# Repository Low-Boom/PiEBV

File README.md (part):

# PiEBV

A USB-controlled pulse-timing box for particle image velocimetry (PIV), built around a Raspberry
Pi Pico 2 W. It triggers two laser drivers and synchronizes up to six event cameras.

> **Hardware status:** Firmware timing has not yet been verified on a physical board. Complete the
> [first-board checks](Hardware.md#first-board-checks) before connecting a laser driver or camera.

## Quick start

With the assembled board, a Pico 2 W, a USB-C PD charger that supplies 15 V, and a micro-USB data
cable:

```
python -m pip install platformio
pio run
```

1. Follow the [first-board checks](Hardware.md#first-board-checks) before applying power or
   connecting equipment.
2. Flash `.pio/build/pico2w/firmware.uf2`: hold **BOOTSEL** while connecting the Pico's micro-USB
   cable, then copy the UF2 to the `RP2350` drive. Flash with the Pico out of the board or J17
   unplugged.
3. Seat the Pico components-up, USB toward the board's left edge. Set J10 to **2-3** and J18, J19
   and J21 to **1-2** for the 50 Ω scope checks; leave J11 empty until instructed to check the outputs.
4. Connect the 15 V charger to J17 and the Pico's micro-USB to the computer. Open the Pico's serial
   port, enable local echo, and send `STATUS`.
5. Follow [Hardware setup](#hardware-setup) to check the laser outputs with a scope before
   connecting laser drivers or cameras.

**Contents:** [Quick start](#quick-start) · [What it does](#what-it-does) ·
[Safety](#safety) · [The board](#the-board) · [Hardware setup](#hardware-setup) ·
[Connecting](#connecting) · [Command reference](#command-reference) ·
[Troubleshooting](#troubleshooting) · [Building from source](#building-from-source) ·
[Repository layout](#repository-layout)

---

## What it does

| Output | Connector | What it is for |
|---|---|---|
| **Laser 1** (CH1) | BNC J7 | Trigger for the first laser driver: a 5 V pulse (with J18 set to match the input), `WIDTH` long, `FREQ` times per second |
| **Laser 2** (CH2) | BNC J8 | Trigger for the second laser driver: the same pulse, starting exactly `DELAY` after Laser 1 |
| **Sync** | Camera ports J1–J6 | A steady 1 MHz clock that all six cameras keep time by |
| **Trigger** (the marker) | Camera ports J1–J6 | A pulse at the same instant as every Laser 1 pulse. Each camera records it as a timestamp in its data. (Jumper J10 can switch the cameras to the Laser 1 pulse itself instead.) |
| **Pixel reset** | Camera ports J1–J6 | Holds the camera sensors blank between flash pairs. Controlled only by PiEBV (`PIXGATE`) |
| **External Sync Out** | BNC J12 | A copy of the camera trigger (the marker, or Laser 1 with J10 on 1-2) for other equipment: a 5 V pulse, with J21 set to match the input |

- Every signal to the cameras is **1.8 V** (IDS cameras, J22 open) or **3.3 V** (Prophesee EVK4
  cameras, J22 fitted). The laser outputs and External Sync Out are **5 V**.
- The camera signal level comes from a power mux (U20). Its default input is 1.8 V: with J22 open,
  two pull-up resistors in parallel (R34 and R70) select 1.8 V. A shunt on J22 pulls the select pin low and selects
  3.3 V.
- Each camera line has a **47 Ω series resistor on the board** (R52–R69), between the buffer and
  the camera port. It terminates the camera cable at the source. The camera cables need no
  resistors.
- The camera lines of each group have **equal length** on the board, from the buffer to the series
  resistor: Sync 74.082 mm, Trigger 43.584 mm, pixel reset 51.472 mm (spread below 0.001 mm in
  each group, KiCad's length reading).
- Times are set in steps of **6.667 ns** (one tick of the Pico's 150 MHz clock), or **3.333 ns**
  with a shunt on the clock jumper J20 (a 300 MHz overclock; see [Jumpers](#jumpers)).
  Every reply shows the exact value the hardware will produce, so you never have to correct for the
  step size.
- Both laser pulses share one `WIDTH` and one `FREQ`.
- The firmware sets **no laser-driver limits** (pulse width, duty, spacing). Set what your driver is
  rated for. It only stops the pulses from running into each other.

PiEBV was designed for two **PicoLas LDP-V** laser-diode drivers (models 10-70 and 240-100) and six
**IDS uEye UE-39B0XCP-E** event cameras. Board revision 2 can also drive six **Prophesee EVK4**
cameras at 3.3 V (see the [EVK4 harness](docs/EVK4_HARNESS.md)). Other drivers with a 5 V trigger input should work too, with
the output mode (J18/J19) set to match their input.

---

## Safety

### The short version

1. **The lasers start off.** At every power-up and every reset the laser outputs are DISARMED. They
   pulse only after you send `ARM`.
2. **Typing `DISARM` stops them at once.**
3. **Three things must all be true** for the lasers to pulse. Remove any one and they stop:
   - the firmware is ARMED;
   - a shunt is on **J11 pins 1-2** (or a closed E-stop switch is wired there);
   - a 15 V USB-C charger is plugged into **J17**.
4. **Unplugging the computer does not stop the lasers.** Use J11 or J17 for that.
5. **Set each output's mode (J18, J19, J21) before you connect anything to it.**
6. **One laser driver per output.** Never split an output with a BNC tee, and never join J7 and J8.
7. **Cameras:** build the harness with wires 2, 3, 4, 5 and 7 only, and set every camera to sync
   slave.

### In detail

**Starting and stopping**

- **`DISARM` always works, immediately.** The six letters D-I-S-A-R-M, in any case and anywhere in
  what you type, disarm the outputs as soon as the last letter reaches the board. You don't need to
  press Enter, as long as your terminal sends each key as you type it (all the terminals listed
  under [USB serial](#usb-serial) do). A monitor with a separate input box, such as the Arduino
  IDE's, sends nothing until you press Enter.
- **The three gates are independent.** Each one on its own holds both outputs at 0 V. The firmware
  can only see the first one, so `ARMED=1` does not by itself mean the outputs are live. The third
  gate (U18) checks that the board's 12 V laser-driver supply is between 10.6 and 13.3 V, which needs
  the 15 V charger.
- **Losing the USB link does not disarm.** If the Pico's USB cable is pulled, the PC goes to sleep
  or a script is killed while ARMED, the board keeps running from J17 and the lasers keep pulsing,
  with no way to send `DISARM`. Stop them in hardware: take the J11 shunt off 1-2, or unplug J17.
- **Before uploading new firmware, send `DISARM`.** The upload restarts the Pico, and a restart in
  the middle of a pulse can stretch that one pulse by an estimated 70–150 ns.
- **Before using a debugger (SWD), send `DISARM` and remove the J11 shunt** (or unplug J17). A
  debugger reset can leave a laser output high for milliseconds.

**Laser outputs**

- **Match the output mode to what you connect.** J18 sets the mode for J7 (Laser 1), J19 for J8
  (Laser 2) and J21 for J12 (External Sync Out) ([details](#jumpers)):

  | Shunt | Mode | Use it for | Into a 50 Ω input | Into a Hi-Z input |
  |---|---|---|---|---|
  | **1-2** | 50 Ω | The LDP-V, or any 50 Ω input | **about 4.8 V** (correct) | about 12 V (too high for 5 V logic) |
  | **2-3** | Hi-Z | TTL or 5 V CMOS inputs, a scope at 1 MΩ | about 2.5 V (too low to fire an LDP-V) | **about 4.8 V** (correct) |
  | none | — | nothing: always fit a shunt | about 3.5 V | about 12 V |

  To fire **one light source with both pulses**, or **two light sources together with the same
  double pulse**, use `COMBINE 1` instead ([Combined mode](#combined-mode-combine)): each output
  then carries both pulses, still one driver per output.

**Cameras and jumpers**

- **Camera pins 1, 6 and 8 are not connected on the board,** so a straight-through ribbon can't
  short the camera's own supplies at the board (pin 1 is the camera's 1.8 V output, pin 8 its USB
  5 V). The remaining risk is in the harness: fit only wires 2, 3, 4, 5 and 7 (or cut 1, 6 and 8),
  and never join pin 1 or 8 to a ground wire. Pin 6 is undocumented: don't assume it is a ground.
- **Set every camera to sync slave.** PiEBV drives the sync pin, so a camera set as sync master would
  fight it.
- **Never fit a shunt across all three pins of J10.**
- **Don't short J12.** External Sync Out can be high for up to half the period (`MARKERWIDTH` is
  limited to 50 % for this reason); into a short its 2 W, 68 Ω resistor then takes up to 1.1 W on
  average (1.45 W with J10 on 1-2 and `COMBINE 1`).

More detail: [Hardware.md](Hardware.md), sections Boot and arming, Laser
interlock and Connectors.

---

## The board

The board is a **EuroCard, 160 × 100 mm**. Orientation used below: the board is landscape (160 mm
wide), seen from the top side. All connectors are on the two short edges: the Pico's micro-USB,
TP3 and, at the bottom, the USB-C connector J17 on the **left** edge, and only the three BNCs on
the **right** edge. The Pico plugs into two horizontal sockets at the top left, with its micro-USB at
the left edge, and the six camera ports run in one row along the bottom. The two USB ports are
labelled on the board: **`CONTROL / PROGRAM — PICO MICRO-USB`** (commands and firmware) and
**`POWER ONLY — USB-C PD 15 V`** (J17). The long (160 mm) edges have no parts within 2.5 mm, so the
board fits EuroCard card guides and slotted enclosures.

```
             +------------------------------------------------------------+
 Pico USB    |= Pico 2 W, in J15 (top row)                        J18 J7 =|  Laser 1 (BNC)
 = CONTROL   |  and J14 (bottom row)        J10 (trigger select)          |
             |= TP3 (1 MHz scope)  J20 (clock)                    J19 J8 =|  Laser 2 (BNC)
             |  J12 offset field            J11 (laser enable)            |
             |                                                   J21 J12 =|  External Sync Out (BNC)
 USB-C       |= J17                                                       |
 = POWER ONLY|       J1   J2   J3   J4   J5   J6   (camera ports)         |
             +------------------------------------------------------------+
```

(Not to scale. J18, J19 and J21 are the output-mode jumpers. J22, at the top centre, sets the camera signal level.
The status LEDs are near the top edge. Images of the board are in
[Hardware.md](Hardware.md#board-views).)

### Connectors

| Ref | What | Connect to | Notes |
|---|---|---|---|
| **J1–J6** | Camera ports 1–6 (2×5 IDC headers) | Each camera's 8-pin I/O cable (header pin *n* = camera pin *n*) | Pin 2, 7 ground · 3 pixel reset · 4 trigger · 5 sync · 1, 6, 8, 9, 10 not connected. All signals **1.8 V** (J22 open, IDS cameras) or **3.3 V** (J22 fitted, Prophesee EVK4 with the [EVK4 harness](docs/EVK4_HARNESS.md)). Each signal has a 47 Ω series resistor on the board. Pin 1 is the top-left pin. |
| **J7** | BNC, Laser 1 (CH1) | First laser driver's trigger input | Mode set by J18 |
| **J8** | BNC, Laser 2 (CH2) | Second laser driver's trigger input | Mode set by J19 |
| **J12** | BNC, External Sync Out | Equipment that must follow the camera trigger (50 Ω or Hi-Z input) | Mode set by J21. See [J12](#j12--external-sync-out) below |
| **J17** | USB-C, **power only** | A USB-C PD charger that offers 15 V | No data. Commands and firmware go through the Pico's own micro-USB. |
| **J10** | Camera trigger source (jumper) | A shunt | See [Jumpers](#jumpers) |
| **J11** | Laser enable (jumper) | A shunt, or a normally-closed E-stop switch | See [Jumpers](#jumpers) |
| **J18**, **J19**, **J21** | Output mode (jumpers; J18 = Laser 1, J19 = Laser 2, J21 = External Sync Out) | A shunt | See [Jumpers](#jumpers) |
| **J20** | Clock jumper, 2-pin header right of the Pico, below the J14 row | Nothing (150 MHz), or a shunt (300 MHz overclock) | See [Jumpers](#jumpers). Leave it open unless that Pico passed the soak test. |
| **TP3** | 2-pin header on the left edge, below the Pico | A scope | Pin 1 = the 1 MHz sync straight from the Pico (3.3 V) · pin 2 = ground |
| **J22** | Camera signal level, 2-pin header at the top centre | Nothing (1.8 V, IDS cameras), or a shunt (3.3 V, Prophesee EVK4) | See [Jumpers](#jumpers). **Never fit it with an IDS camera connected.** |
| **TP4–TP9** | Bare test pads at the top centre, marked `12V`, `5V`, `3V3`, `1V8`, `VCAM`, `GND` | A multimeter | Supply rails |

#### J12 — External Sync Out

**A copy of the camera trigger, for other equipment.** J12 pulses whenever the cameras' trigger
lines do: with every marker (J10 on 2-3, also while DISARMED), or with every Laser 1 pulse (J10 on
1-2, only while ARMED). It is built like a laser output, so the levels are the same:

- **J21 on 1-2 (50 Ω mode):** about 4.8 V (4.53–5.14 V) into a 50 Ω input.
- **J21 on 2-3 (Hi-Z mode):** about 4.8 V (4.55–5.08 V) into a high-impedance input, from a ~50 Ω
  source, so long cables don't overshoot.
- It needs the 15 V charger on J17; on the Pico's USB alone J12 stays at 0 V.
- J12 and the cameras' trigger are offset by a fixed delay: J12 passes a 12 V driver, the camera
  trigger lines pass the camera buffers. It is typically about +10 ns (J12 later), but anywhere from
  −9 to +26 ns from part to part. **Measure it once on each board** and write it in the `J12-TRIG OFFSET (MEASURED)` field on the silkscreen (left area, below TP3), if your
  instrument must line up with the cameras to better than ~30 ns (Hardware.md, First-board checks).
- One device per output, no BNC tee, and don't short it (see [Safety](#safety)).

The board has no pixel-reset input any more: PiEBV alone controls the camera pixel reset
([`PIXGATE`](#pixel-reset-gate-pixgate)).

### Jumpers

J10 and J11 are numbered 1-2-3 from **left to right**. J18, J19 and J21 stand upright between the
large resistors and the BNCs: J18's and J21's pin 1 is at the top, J19's at the bottom. Pin 1 always
has the square pad.

| Jumper | Board label | Shunt on 1-2 | Shunt on 2-3 | No shunt |
|---|---|---|---|---|
| **J11** laser enable | `ON` … `OFF` | **Lasers enabled** (the firmware must also be ARMED) | Lasers off | Lasers off (fail-safe) |
| **J10** camera trigger | `CH1 TRG MKR` | Cameras triggered by every Laser 1 pulse (only while ARMED) | **Cameras triggered by the marker** (normal) | No camera triggers |
| **J18** Laser 1 output mode | `50Ω` by pins 1-2, `HiZ` by 2-3 | **50 Ω mode** (normal, for the LDP-V) | Hi-Z mode | Wrong for everything: always fit a shunt |
| **J19** Laser 2 output mode | as J18 | as J18 | as J18 | as J18 |
| **J21** External Sync Out mode | as J18 | **50 Ω mode** (normal) | Hi-Z mode | as J18 |
| **J20** clock jumper (2 pins) | `CLOCK JUMPER` · `OPEN = 150 MHz` · `FIT = 300 MHz (OVERCLOCK)` | Shunt fitted: 300 MHz overclock (soak-test the Pico first) | – | **150 MHz, the rated clock** (normal) |
| **J22** camera signal level (2 pins) | `CAMERA I/O LEVEL (J22)` · `OPEN = 1V8  IDS` · `SHUNT = 3V3  EVK4` | Shunt fitted: **3.3 V** on all six camera ports (Prophesee EVK4). The blue LED `3V3` is lit. | – | **1.8 V** (IDS cameras; normal) |

**J11 — laser enable and E-stop.** Labelled `LASER INTERLOCK: ON = 1-2` and
`E-STOP: NC SWITCH ACROSS 1-2`. For an emergency-stop switch, take the shunt off and wire a
**normally-closed** switch across pins 1 and 2. Closed, the lasers are enabled (if also ARMED and
powered). Pressing the switch **or** breaking its cable opens the circuit and turns the lasers off,
so the stop is fail-safe.

**J22 — camera signal level.** J22 sets the level of the Sync, Trigger and pixel-reset lines on
**all six** camera ports. Open, the level is 1.8 V, which the IDS cameras need. With a shunt, the
level is 3.3 V, which the Prophesee EVK4 needs. **3.3 V can destroy the 1.8 V inputs of an IDS
camera:** fit the shunt only when no IDS camera is connected, and do not use IDS and EVK4 cameras
together. The blue LED marked `3V3` next to J22 is lit when the level is 3.3 V: look at it before
you connect a camera. Before you connect an IDS camera, also measure the test pad `VCAM` (TP8)
with a meter: it must be 1.8 V with J22 open. Change J22 with the power off. An EVK4 camera needs the
[EVK4 harness](docs/EVK4_HARNESS.md); it has no pixel-reset input, so `PIXGATE` has no effect on it.
The harness has no resistors: the series resistors are on the board.

**J10 — camera trigger source.** Labelled `CH1 TRG MKR` under the pins and
`CAMERA TRIGGER: TRG-MKR = MARKER / TRG-CH1 = LASER 1` beside them. The middle pin (`TRG`) feeds the
trigger input of all six cameras and External Sync Out (J12).
- `TRG` to `MKR` (2-3, normal): the marker. It rises with every Laser 1 pulse, has its own width
  (`MARKERWIDTH`, 2 µs by default) and keeps running while DISARMED.
- `TRG` to `CH1` (1-2): the Laser 1 pulse itself, so only while ARMED. The cameras need a trigger
  pulse of at least 500 ns, so this is only dependable with `WIDTH` ≥ 500 ns.
- Never join all three pins.

**J18 / J19 — laser output mode.** Labelled `LASER 1 OUT` / `LASER 2 OUT`, with `50Ω` and `HiZ`
next to the pin pairs.
- **1-2, 50 Ω mode:** about 4.8 V (4.53–5.14 V) into a 50 Ω input. Use it for the PicoLas LDP-V and
  anything else with a 50 Ω input.
- **2-3, Hi-Z mode:** about 4.8 V (4.55–5.08 V) into a high-impedance input. The output is matched
  to 50 Ω coax, so even a long cable to an unterminated input gives a clean edge (at most ~5 %
  overshoot into a scope's 1 MΩ ∥ 15 pF).
  Use it for TTL or 5 V CMOS inputs, scopes at 1 MΩ and other instruments that don't terminate.
- **The wrong mode** gives the wrong voltage (see the table under [Safety](#in-detail)): an LDP-V on
  Hi-Z mode sees 2.3–2.6 V and won't fire, and a 5 V logic input on 50 Ω mode sees ~12 V, which can
  damage it. Don't use Hi-Z mode as a way to keep a laser off: J11 is the interlock.
- The two jumpers are independent, so one output can drive an LDP-V and the other a logic input. The
  firmware can't see them, and the pulse timing is the same in both modes.

**J20 — clock jumper (300 MHz overclock).** A 2-pin header right of the Pico, below the J14 row.
Pin 1 (square pad, the lower pin) goes to GP10 through R29 (1 kΩ, which protects GP10 if a
program drives it), pin 2 is GND. A shunt on J20, read at every start (power-up or reset),
runs the Pico at 300 MHz instead of 150 MHz, so every time setting has 3.333 ns steps instead of
6.667 ns. That is twice the chip's rated speed: soak-test each Pico first, as described in
[Hardware.md](Hardware.md#clock-jumper-j20-300-mhz-overclock). No shunt (the default) is the
rated 150 MHz. After any watchdog restart the Pico stays at 150 MHz until it is power-cycled.
`STATUS` shows the clock in `CLK` and `CLKMODE`.

### Status LEDs

The LEDs near the top edge show the state of the board.

| LED | Colour | Meaning when lit |
|---|---|---|
| `12V OK` | green | The USB-C charger gave 15 V and the 12 V supply of the output drivers is good. Dark: the laser outputs and J12 cannot pulse. |
| `ARMED` | red | The lasers can fire: the firmware is ARMED, J11 is on 1-2 (or the E-stop switch is closed) and `12V OK` is lit. |
| `3V3` | blue | The camera ports are at 3.3 V (J22 fitted). Dark: 1.8 V. |
| `L1`, `L2` | red | A pulse left the Laser 1 / Laser 2 output driver. One flash for each pulse; on continuously above about 70 pulses a second. |
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
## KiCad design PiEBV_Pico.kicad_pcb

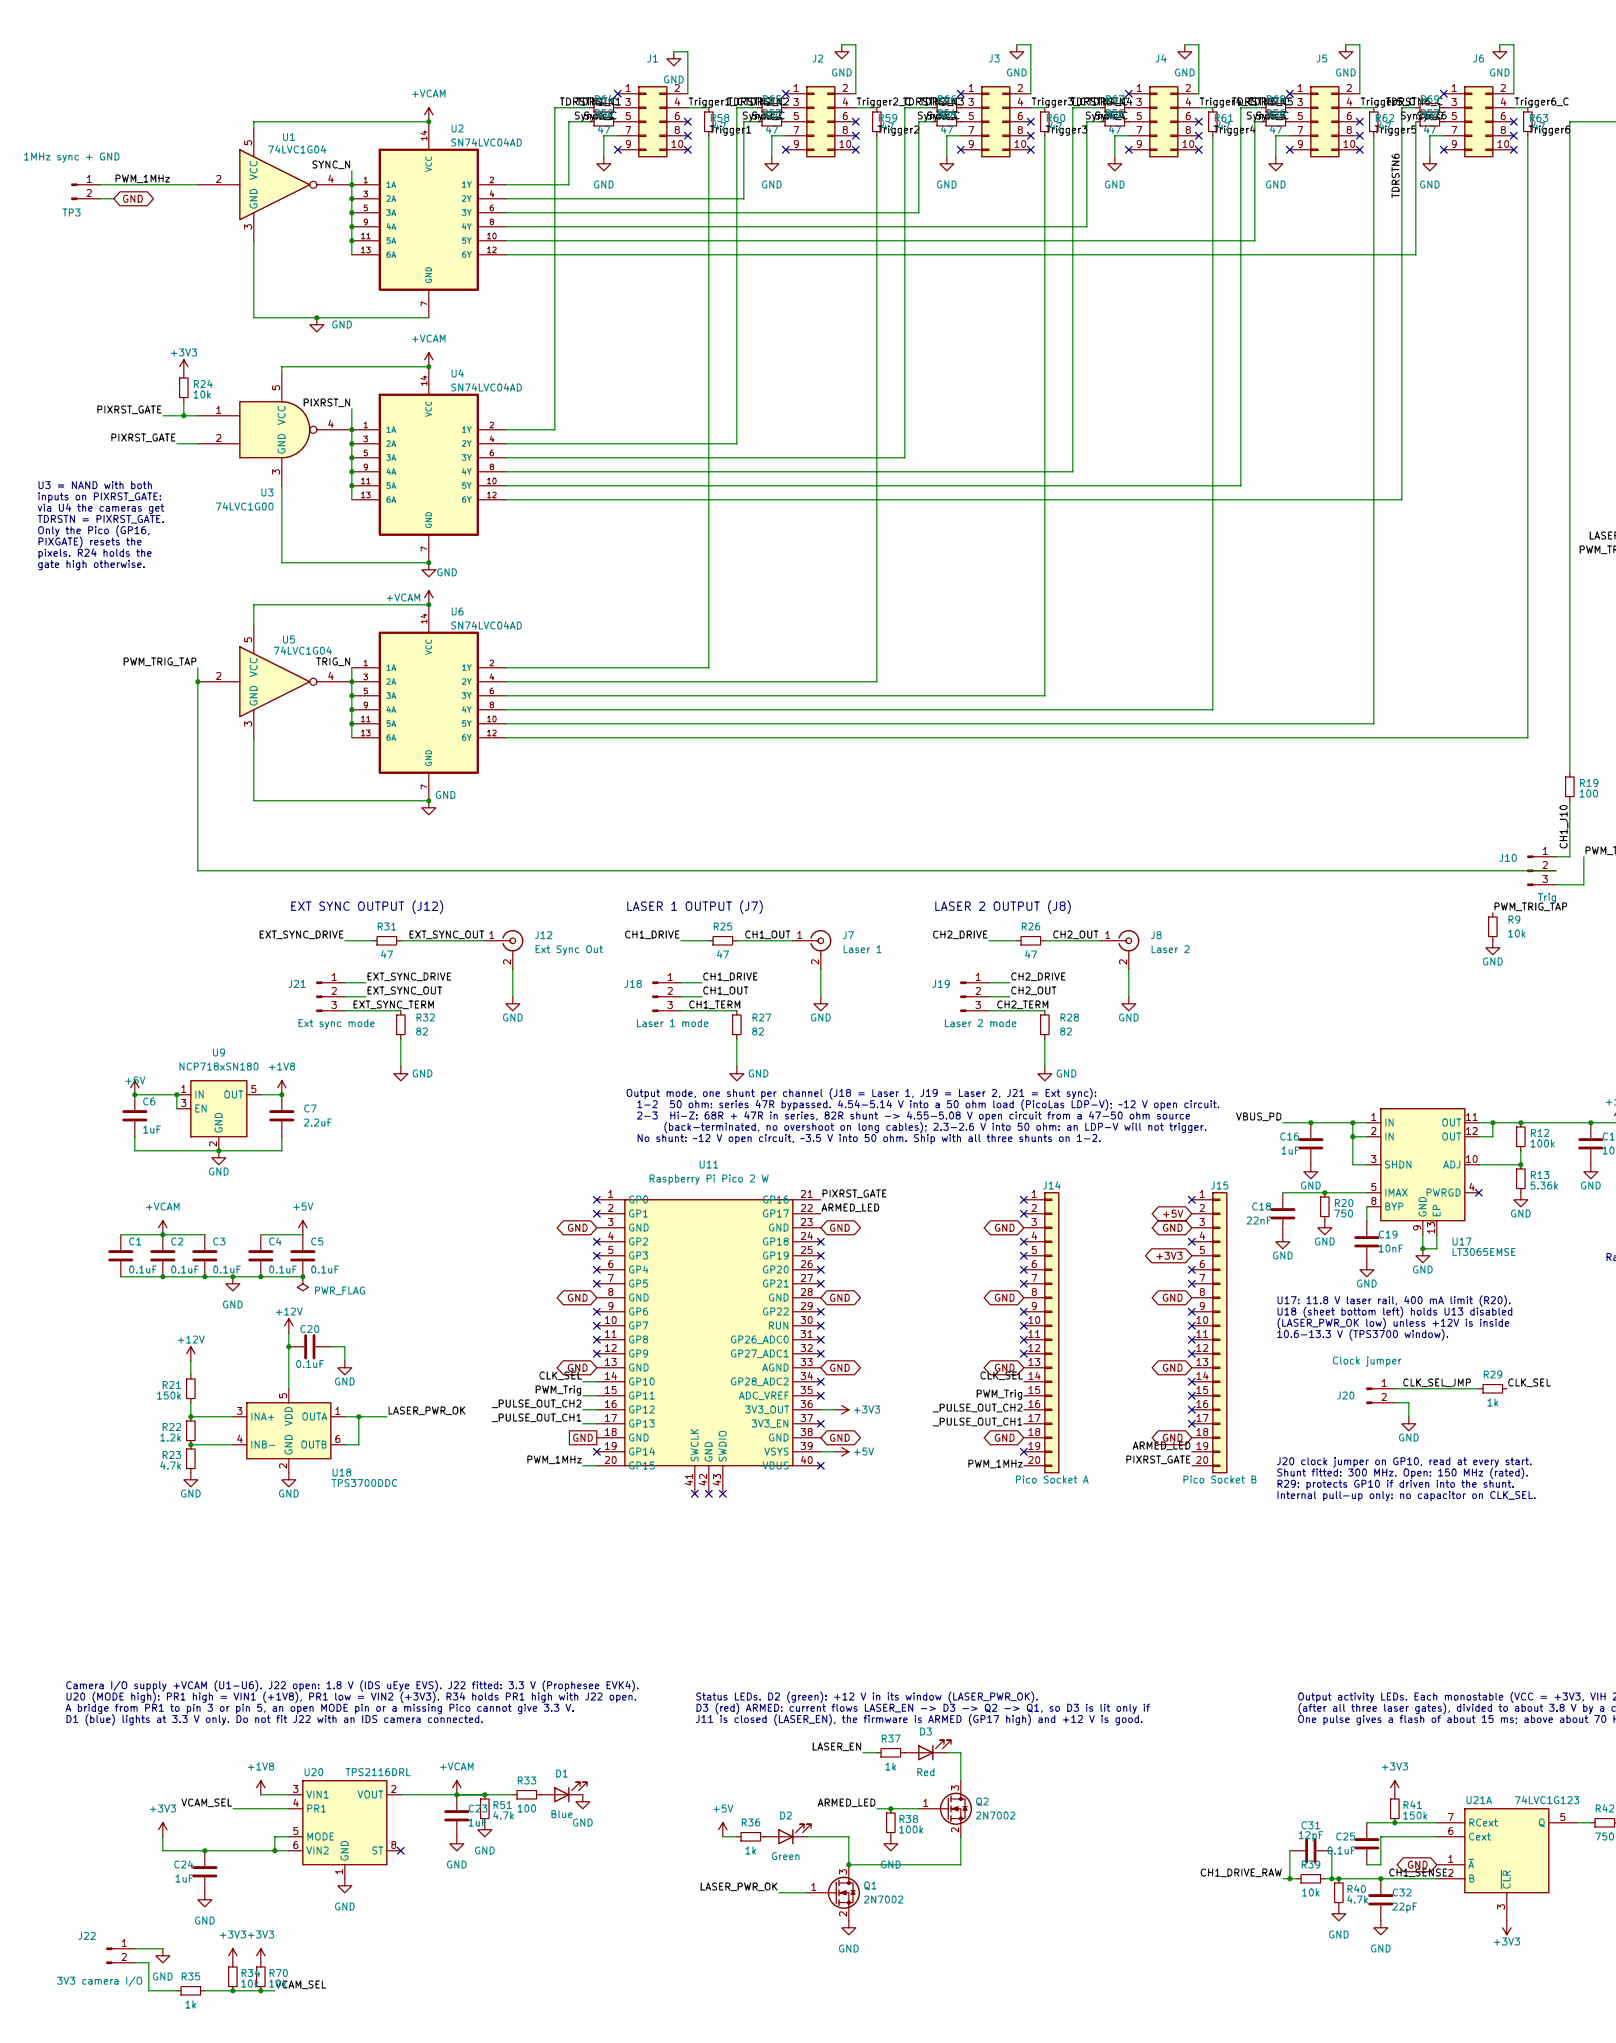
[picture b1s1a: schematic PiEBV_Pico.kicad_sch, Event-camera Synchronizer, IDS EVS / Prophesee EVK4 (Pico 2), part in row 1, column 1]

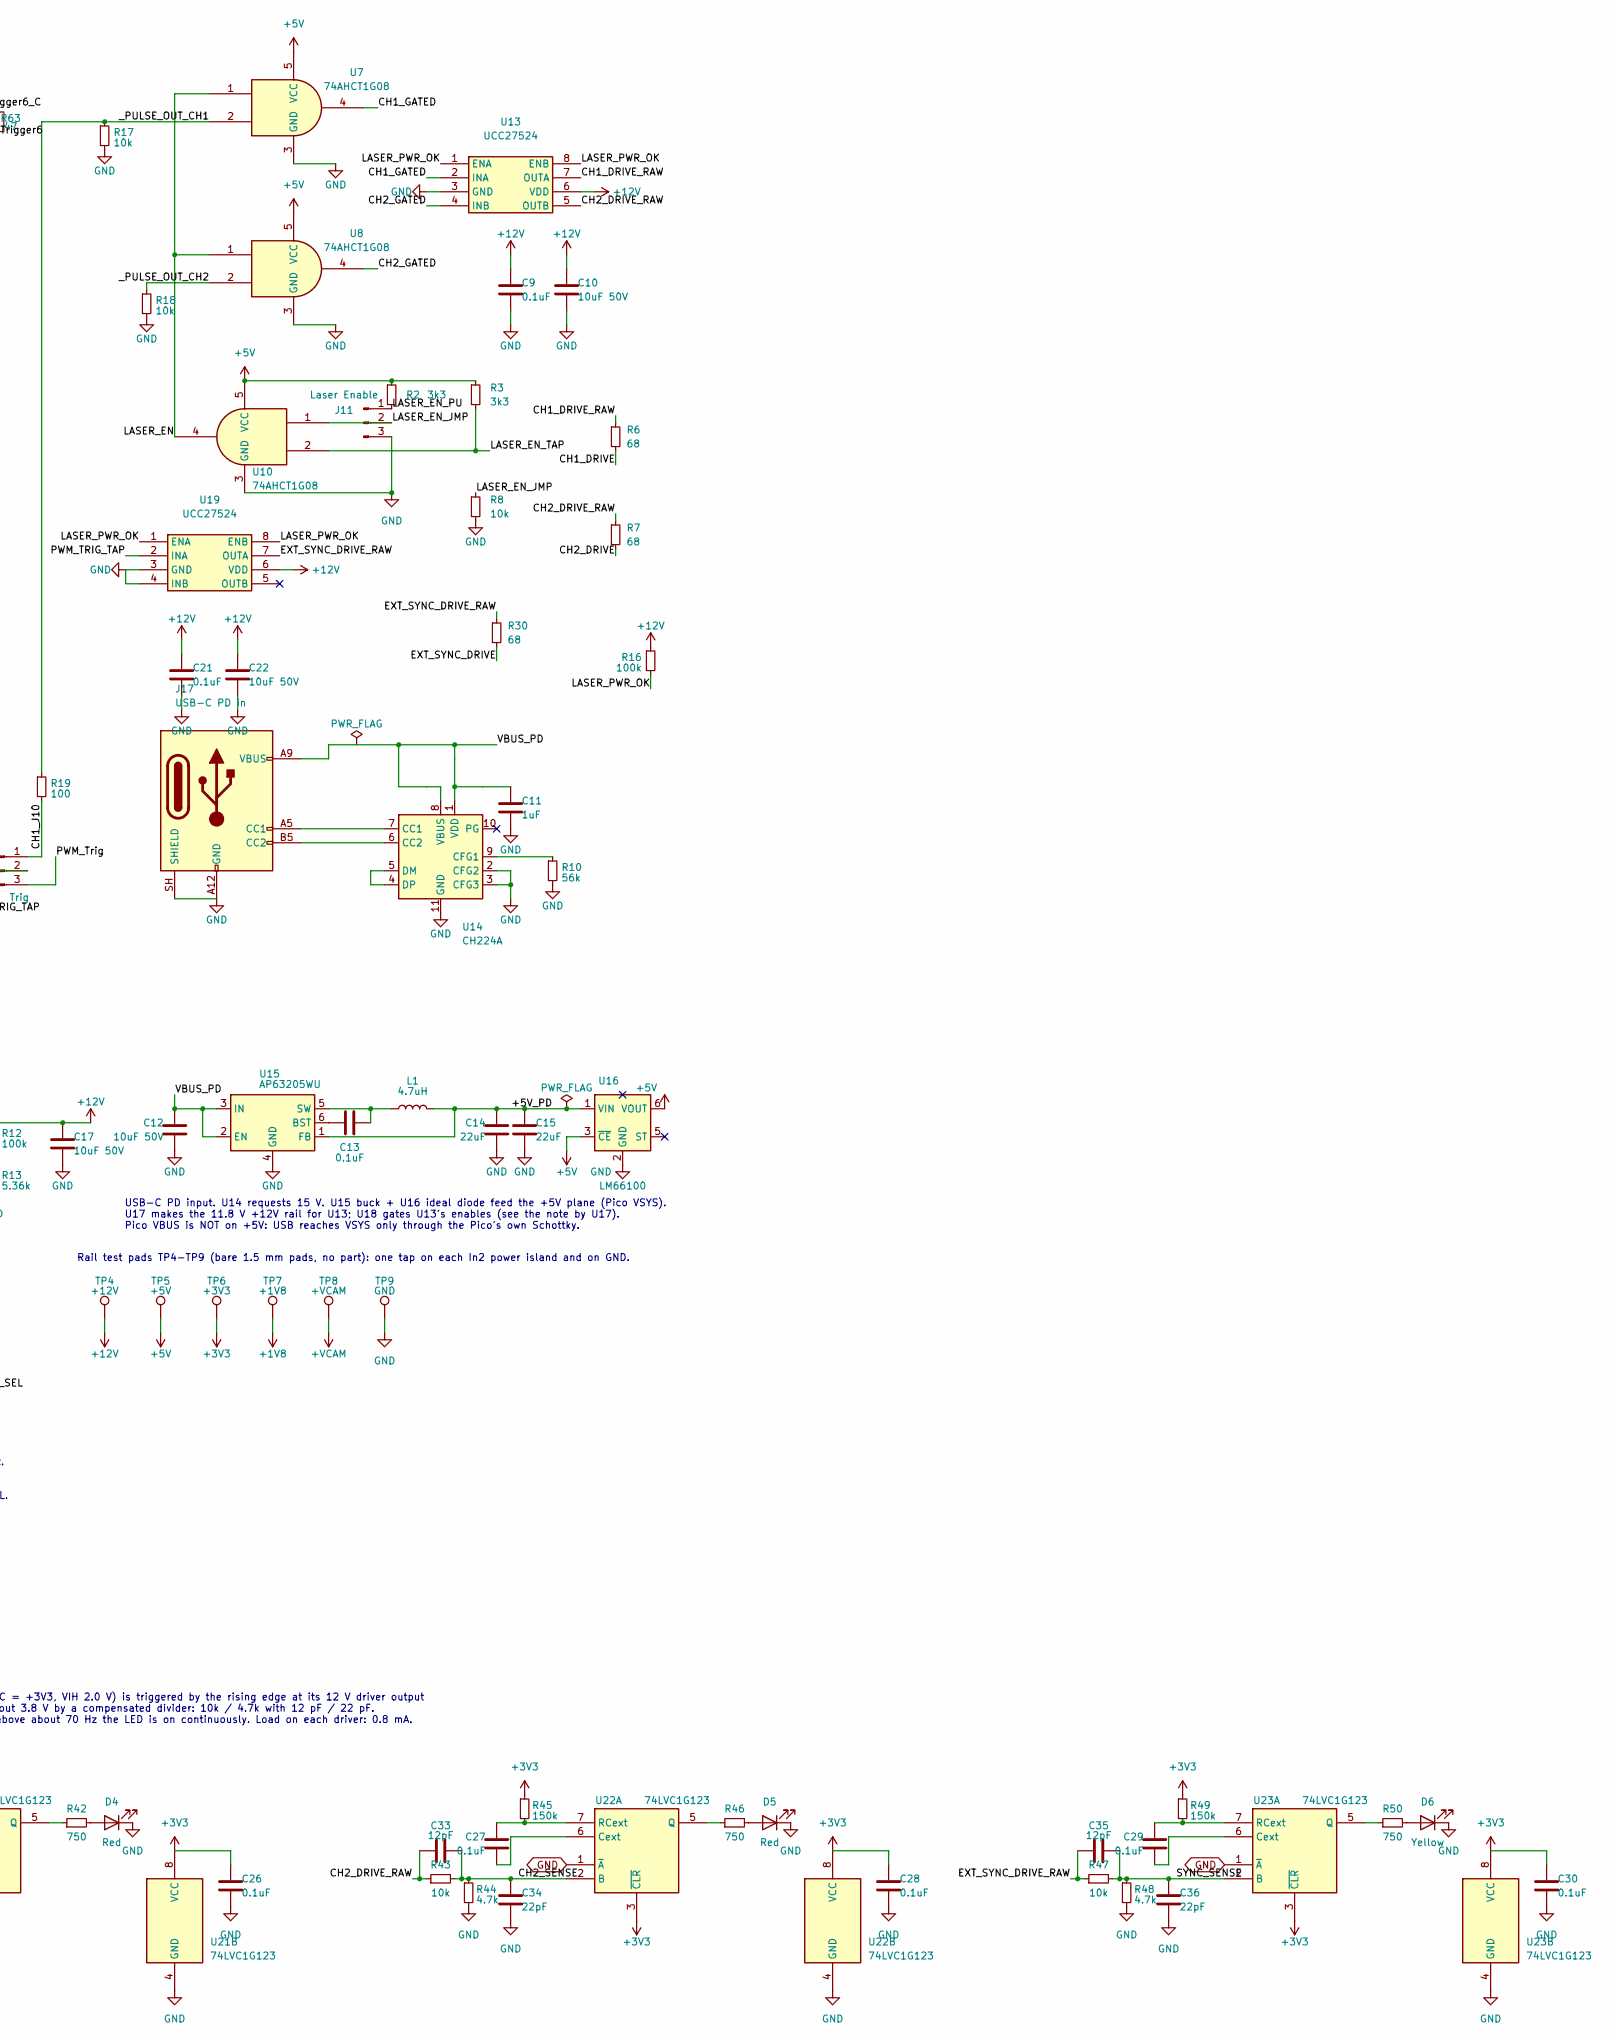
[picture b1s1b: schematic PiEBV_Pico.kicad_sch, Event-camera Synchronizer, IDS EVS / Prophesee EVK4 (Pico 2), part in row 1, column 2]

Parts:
C1, C2, C3, C4, C5, C9, C13, C20, C21, C25, C26, C27, C28, C29, C30: 0.1uF; C_0805_2012Metric_Pad1.18x1.45mm_HandSolder
C6, C11, C16, C23, C24: 1uF; C_0805_2012Metric_Pad1.18x1.45mm_HandSolder
C7: 2.2uF; C_0805_2012Metric_Pad1.18x1.45mm_HandSolder
C10, C12, C17, C22: 10uF 50V; C_1206_3216Metric_Pad1.33x1.80mm_HandSolder
C14, C15: 22uF; C_0805_2012Metric_Pad1.18x1.45mm_HandSolder
C18: 22nF; C_0805_2012Metric_Pad1.18x1.45mm_HandSolder
C19: 10nF; C_0805_2012Metric_Pad1.18x1.45mm_HandSolder
C31, C33, C35: 12pF; C_0805_2012Metric_Pad1.18x1.45mm_HandSolder
C32, C34, C36: 22pF; C_0805_2012Metric_Pad1.18x1.45mm_HandSolder
D1: Blue; LED_0805_2012Metric_Pad1.15x1.40mm_HandSolder
D2: Green; LED_0805_2012Metric_Pad1.15x1.40mm_HandSolder
D3, D4, D5: Red; LED_0805_2012Metric_Pad1.15x1.40mm_HandSolder
D6: Yellow; LED_0805_2012Metric_Pad1.15x1.40mm_HandSolder
J1, J2, J3, J4, J5, J6: Conn_02x05_Odd_Even; IDC-Header_2x05_P2.54mm_Vertical
J7: Laser 1; BNC_Kinghelm_KH-BNC50-3511_Horizontal
J8: Laser 2; BNC_Kinghelm_KH-BNC50-3511_Horizontal
J10: Trig; PinHeader_1x03_P2.54mm_Vertical
J11: Laser Enable; PinHeader_1x03_P2.54mm_Vertical
J12: Ext Sync Out; BNC_Kinghelm_KH-BNC50-3511_Horizontal
J14: Pico Socket A; PinSocket_1x20_P2.54mm_Vertical
J15: Pico Socket B; PinSocket_1x20_P2.54mm_Vertical
J17: USB-C PD in; USB_C_Receptacle_HRO_TYPE-C-31-M-17_EdgeTrim
J18: Laser 1 mode; PinHeader_1x03_P2.54mm_Vertical
J19: Laser 2 mode; PinHeader_1x03_P2.54mm_Vertical
J20: Clock jumper; PinHeader_1x02_P2.54mm_Vertical
J21: Ext sync mode; PinHeader_1x03_P2.54mm_Vertical
J22: 3V3 camera I/O; PinHeader_1x02_P2.54mm_Vertical
L1: 4.7uH; L_Cenker_CKCS4030
Q1, Q2: 2N7002; SOT-23
R2, R3: 3k3; R_0805_2012Metric_Pad1.20x1.40mm_HandSolder
R6, R7, R30: 68; R_2512_6332Metric_Pad1.40x3.35mm_HandSolder
R8, R9, R17, R18, R24, R34, R39, R43, R47, R70: 10k; R_0805_2012Metric_Pad1.20x1.40mm_HandSolder
R10: 56k; R_0805_2012Metric_Pad1.20x1.40mm_HandSolder
R12, R16, R38: 100k; R_0805_2012Metric_Pad1.20x1.40mm_HandSolder
R13: 5.36k; R_0805_2012Metric_Pad1.20x1.40mm_HandSolder
R19, R33: 100; R_0805_2012Metric_Pad1.20x1.40mm_HandSolder
R20, R42, R46, R50: 750; R_0805_2012Metric_Pad1.20x1.40mm_HandSolder
R21, R41, R45, R49: 150k; R_0805_2012Metric_Pad1.20x1.40mm_HandSolder
R22: 1.2k; R_0805_2012Metric_Pad1.20x1.40mm_HandSolder
R23, R40, R44, R48, R51: 4.7k; R_0805_2012Metric_Pad1.20x1.40mm_HandSolder
R25, R26, R31: 47; R_2512_6332Metric_Pad1.40x3.35mm_HandSolder
R27, R28, R32: 82; R_2512_6332Metric_Pad1.40x3.35mm_HandSolder
R29, R35, R36, R37: 1k; R_0805_2012Metric_Pad1.20x1.40mm_HandSolder
R52, R53, R54, R55, R56, R57, R58, R59, R60, R61, R62, R63, R64, R65, R66, R67, R68, R69: 47; R_0805_2012Metric_Pad1.20x1.40mm_HandSolder
TP3: 1MHz sync + GND; PinHeader_1x02_P2.54mm_Horizontal_EdgeTrim
TP4: +12V; TestPoint_Pad_D1.5mm
TP5: +5V; TestPoint_Pad_D1.5mm
TP6: +3V3; TestPoint_Pad_D1.5mm
TP7: +1V8; TestPoint_Pad_D1.5mm
TP8: +VCAM; TestPoint_Pad_D1.5mm
TP9: GND; TestPoint_Pad_D1.5mm
U1, U5: 74LVC1G04; SOT-23-5_HandSoldering
U2, U4, U6: SN74LVC04AD; SOIC127P600X175-14N
U3: 74LVC1G00; SOT-23-5_HandSoldering
U7, U8, U10: 74AHCT1G08; SOT-23-5_HandSoldering
U9: NCP718xSN180; SOT-23-5_HandSoldering
U11: Raspberry Pi Pico 2 W
U13, U19: UCC27524; SOIC-8_3.9x4.9mm_P1.27mm
U14: CH224A; SSOP-10-1EP_3.9x4.9mm_P1mm_EP2.1x3.3mm
U15: AP63205WU; TSOT-23-6_HandSoldering
U16: LM66100; SOT-363_SC-70-6
U17: LT3065EMSE; MSOP-12-1EP_3x4.039mm_P0.65mm_EP1.651x2.845mm
U18: TPS3700DDC; SOT-23-6
U20: TPS2116DRL; SOT-583-8
U21, U22, U23: 74LVC1G123; SSOP-8_2.95x2.8mm_P0.65mm

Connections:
+1V8: C7.1, TP7.1, U9.5 (VCC), U20.3 (VIN1)
+3V3: C24.1, C26.1, C28.1, C30.1, J15.5, R24.1, R34.1, R41.1, R45.1, R49.1, R70.1, TP6.1, U11.36 (3V3_OUT), U20.5 (MODE), U20.6 (VIN2), U21.3 (~CLR), U21.8 (VCC), U22.3 (~CLR), U22.8 (VCC), U23.3 (~CLR), U23.8 (VCC)
+5V: C4.1, C5.1, C6.1, J15.2, R2.1, R3.1, R36.1, TP5.1, U7.5 (VCC), U8.5 (VCC), U9.1 (IN), U9.3 (GND), U10.5 (VCC), U11.39 (VSYS), U16.3 (~CE), U16.6 (VOUT)
+5V_PD: C14.1, C15.1, L1.2, U15.1 (FB), U16.1 (VIN)
+12V: C9.2, C10.2, C17.1, C20.1, C21.2, C22.2, R12.1, R16.1, R21.1, TP4.1, U13.6 (VDD), U17.11 (OUT), U17.12 (OUT), U18.5 (VDD), U19.6 (VDD)
+VCAM: C1.1, C2.1, C3.1, C23.1, R33.1, R51.1, TP8.1, U1.5 (VCC), U2.14 (VCC), U3.5 (VCC), U4.14 (VCC), U5.5 (VCC), U6.14 (VCC), U20.2 (VOUT), U20.7 (VOUT)
ARMED_LED: J15.19, Q2.1 (G), R38.1, U11.22 (GP17)
CH1_DRIVE: J18.1, R6.2, R25.1
CH1_DRIVE_RAW: C31.1, R6.1, R39.1, U13.7 (OUTA)
CH1_GATED: U7.4, U13.2 (INA)
CH1_J10: J10.1, R19.2
CH1_OUT: J7.1 (In), J18.2, R25.2
CH1_SENSE: C31.2, C32.1, R39.2, R40.1, U21.2 (B)
CH1_TERM: J18.3, R27.1
CH2_DRIVE: J19.1, R7.2, R26.1
CH2_DRIVE_RAW: C33.1, R7.1, R43.1, U13.5 (OUTB)
CH2_GATED: U8.4, U13.4 (INB)
CH2_OUT: J8.1 (In), J19.2, R26.2
CH2_SENSE: C33.2, C34.1, R43.2, R44.1, U22.2 (B)
CH2_TERM: J19.3, R28.1
CLK_SEL: J14.14, R29.2, U11.14 (GP10)
CLK_SEL_JMP: J20.1, R29.1
EXT_SYNC_DRIVE: J21.1, R30.2, R31.1
EXT_SYNC_DRIVE_RAW: C35.1, R30.1, R47.1, U19.7 (OUTA)
EXT_SYNC_OUT: J12.1 (In), J21.2, R31.2
EXT_SYNC_TERM: J21.3, R32.1
GND: C1.2, C2.2, C3.2, C4.2, C5.2, C6.2, C7.2, C9.1, C10.1, C11.2, C12.2, C14.2, C15.2, C16.2, C17.2, C18.2, C19.2, C20.2, C21.1, C22.1, C23.2, C24.2, C26.2, C28.2, C30.2, C32.2, C34.2, C36.2, D1.1 (K), D4.1 (K), D5.1 (K), D6.1 (K), J1.2, J1.7, J2.2, J2.7, J3.2, J3.7, J4.2, J4.7, J5.2, J5.7, J6.2, J6.7, J7.2 (Ext), J8.2 (Ext), J11.3, J12.2 (Ext), J14.3, J14.8, J14.13, J14.18, J15.3, J15.8, J15.13, J15.18, J17.A12 (GND), J17.B12 (GND), J17.SH (SHIELD), J20.2, J22.1, Q1.2 (S), R8.2, R9.2, R10.2, R13.2, R17.2, R18.2, R20.2, R23.2, R27.2, R28.2, R32.2, R38.2, R40.2, R44.2, R48.2, R51.2, TP3.2, TP9.1, U1.3 (GND), U2.7 (GND), U3.3 (GND), U4.7 (GND), U5.3 (GND), U6.7 (GND), U7.3 (GND), U8.3 (GND), U9.2 (GND), U10.3 (GND), U11.3 (GND), U11.8 (GND), U11.13 (GND), U11.18 (GND), U11.23 (GND), U11.28 (GND), U11.33 (AGND), U11.38 (GND), U13.3 (GND), U14.2 (CFG2), U14.3 (CFG3), U14.11 (GND), U15.4 (GND), U16.2 (GND), U17.9 (GND), U17.13 (EP), U18.2 (GND), U19.3 (GND), U19.4 (INB), U20.1 (GND), U21.1 (~A), U21.4 (GND), U22.1 (~A), U22.4 (GND), U23.1 (~A), U23.4 (GND)
LASER_EN: R37.1, U7.1, U8.1, U10.4
LASER_EN_JMP: J11.2, R8.1, U10.1
LASER_EN_PU: J11.1, R2.2
LASER_EN_TAP: R3.2, U10.2
LASER_PWR_OK: Q1.1 (G), R16.2, U13.1 (ENA), U13.8 (ENB), U18.1 (OUTA), U18.6 (OUTB), U19.1 (ENA), U19.8 (ENB)
unnamed: D1.2 (A), R33.2
unnamed: D2.2 (A), R36.2
unnamed: D2.1 (K), Q1.3 (D), Q2.2 (S)
unnamed: D3.2 (A), R37.2
unnamed: D3.1 (K), Q2.3 (D)
unnamed: D4.2 (A), R42.2
unnamed: D5.2 (A), R46.2
unnamed: D6.2 (A), R50.2
unnamed: J17.A5 (CC1), U14.7 (CC1)
unnamed: J17.B5 (CC2), U14.6 (CC2)
unnamed: J22.2, R35.1
unnamed: R10.1, U14.9 (CFG1)
unnamed: U14.4 (DP), U14.5 (DM)
unnamed: C13.1, U15.6 (BST)
unnamed: C13.2, L1.1, U15.5 (SW)
unnamed: R12.2, R13.1, U17.10 (ADJ)
unnamed: C19.1, U17.8 (BYP)
unnamed: C18.1, R20.1, U17.5 (IMAX)
unnamed: R21.2, R22.1, U18.3 (INA+)
unnamed: R22.2, R23.1, U18.4 (INB-)
unnamed: C25.2, U21.6 (Cext)
unnamed: R42.1, U21.5 (Q)
unnamed: C25.1, R41.2, U21.7 (RCext)
unnamed: C27.2, U22.6 (Cext)
unnamed: R46.1, U22.5 (Q)
unnamed: C27.1, R45.2, U22.7 (RCext)
unnamed: C29.2, U23.6 (Cext)
unnamed: R50.1, U23.5 (Q)
unnamed: C29.1, R49.2, U23.7 (RCext)
PIXRST_GATE: J15.20, R24.2, U3.1 (NC), U3.2, U11.21 (GP16)
PIXRST_N: U3.4, U4.1 (1A), U4.3 (2A), U4.5 (3A), U4.9 (4A), U4.11 (5A), U4.13 (6A)
PWM_1MHz: J14.20, TP3.1, U1.2, U11.20 (GP15)
PWM_TRIG_TAP: J10.2, R9.1, U5.2, U19.2 (INA)
PWM_Trig: J10.3, J14.15, U11.15 (GP11)
SYNC_N: U1.4, U2.1 (1A), U2.3 (2A), U2.5 (3A), U2.9 (4A), U2.11 (5A), U2.13 (6A)
SYNC_SENSE: C35.2, C36.1, R47.2, R48.1, U23.2 (B)
Sync1: R52.1, U2.2 (1Y)
Sync1_C: J1.5, R52.2
Sync2: R53.1, U2.4 (2Y)
Sync2_C: J2.5, R53.2
Sync3: R54.1, U2.6 (3Y)
Sync3_C: J3.5, R54.2
Sync4: R55.1, U2.8 (4Y)
Sync4_C: J4.5, R55.2
Sync5: R56.1, U2.10 (5Y)
Sync5_C: J5.5, R56.2
Sync6: R57.1, U2.12 (6Y)
Sync6_C: J6.5, R57.2
TDRSTN1: R64.1, U4.2 (1Y)
TDRSTN1_C: J1.3, R64.2
TDRSTN2: R65.1, U4.4 (2Y)
TDRSTN2_C: J2.3, R65.2
TDRSTN3: R66.1, U4.6 (3Y)
TDRSTN3_C: J3.3, R66.2
TDRSTN4: R67.1, U4.8 (4Y)
TDRSTN4_C: J4.3, R67.2
TDRSTN5: R68.1, U4.10 (5Y)
TDRSTN5_C: J5.3, R68.2
TDRSTN6: R69.1, U4.12 (6Y)
TDRSTN6_C: J6.3, R69.2
TRIG_N: U5.4, U6.1 (1A), U6.3 (2A), U6.5 (3A), U6.9 (4A), U6.11 (5A), U6.13 (6A)
Trigger1: R58.2, U6.2 (1Y)
Trigger1_C: J1.4, R58.1
Trigger2: R59.2, U6.4 (2Y)
Trigger2_C: J2.4, R59.1
Trigger3: R60.2, U6.6 (3Y)
Trigger3_C: J3.4, R60.1
Trigger4: R61.2, U6.8 (4Y)
Trigger4_C: J4.4, R61.1
Trigger5: R62.2, U6.10 (5Y)
Trigger5_C: J5.4, R62.1
Trigger6: R63.2, U6.12 (6Y)
Trigger6_C: J6.4, R63.1
VBUS_PD: C11.1, C12.1, C16.1, J17.A9 (VBUS), J17.B9 (VBUS), U14.1 (VDD), U14.8 (VBUS), U15.2 (EN), U15.3 (IN), U17.1 (IN), U17.2 (IN), U17.3 (SHDN)
VCAM_SEL: R34.2, R35.2, R70.2, U20.4 (PR1)
_PULSE_OUT_CH1: J14.17, R17.1, R19.1, U7.2, U11.17 (GP13)
_PULSE_OUT_CH2: J14.16, R18.1, U8.2, U11.16 (GP12)

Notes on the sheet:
USB-C PD input. U14 requests 15 V. U15 buck + U16 ideal diode feed the +5V plane (Pico VSYS). U17 makes the 11.8 V +12V rail for U13; U18 gates U13's enables (see the note by U17). Pico VBUS is NOT on +5V: USB reaches VSYS only through the Pico's own Schottky.
LASER 1 OUTPUT (J7)
LASER 2 OUTPUT (J8)
Output mode, one shunt per channel (J18 = Laser 1, J19 = Laser 2, J21 = Ext sync): 1-2 50 ohm: series 47R bypassed. 4.54-5.14 V into a 50 ohm load (PicoLas LDP-V); ~12 V open circuit. 2-3 Hi-Z: 68R + 47R in series, 82R shunt -> 4.55-5.08 V open circuit from a 47-50 ohm source (back-terminated, no o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
U3 = NAND with both inputs on PIXRST_GATE: via U4 the cameras get TDRSTN = PIXRST_GATE. Only the Pico (GP16, PIXGATE) resets the pixels. R24 holds the gate high otherwise.
U17: 11.8 V laser rail, 400 mA limit (R20). U18 (sheet bottom left) holds U13 disabled (LASER_PWR_OK low) unless +12V is inside 10.6-13.3 V (TPS3700 window).
J20 clock jumper on GP10, read at every start. Shunt fitted: 300 MHz. Open: 150 MHz (rated). R29: protects GP10 if driven into the shunt. Internal pull-up only: no capacitor on CLK_SEL.
EXT SYNC OUTPUT (J12)
Camera I/O supply +VCAM (U1-U6). J22 open: 1.8 V (IDS uEye EVS). J22 fitted: 3.3 V (Prophesee EVK4). U20 (MODE high): PR1 high = VIN1 (+1V8), PR1 low = VIN2 (+3V3). R34 holds PR1 high with J22 open. A bridge from PR1 to pin 3 or pin 5, an open MODE pin or a missing Pico cannot give 3.3 V. D1 (blue)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
Status LEDs. D2 (green): +12 V in its window (LASER_PWR_OK). D3 (red) ARMED: current flows LASER_EN -> D3 -> Q2 -> Q1, so D3 is lit only if J11 is closed (LASER_EN), the firmware is ARMED (GP17 high) and +12 V is good.
Output activity LEDs. Each monostable (VCC = +3V3, VIH 2.0 V) is triggered by the rising edge at its 12 V driver output (after all three laser gates), divided to about 3.8 V by a compensated divider: 10k / 4.7k with 12 pF / 22 pF. One pulse gives a flash of about 15 ms; above about 70 Hz the LED is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
Rail test pads TP4-TP9 (bare 1.5 mm pads, no part): one tap on each In2 power island and on GND.

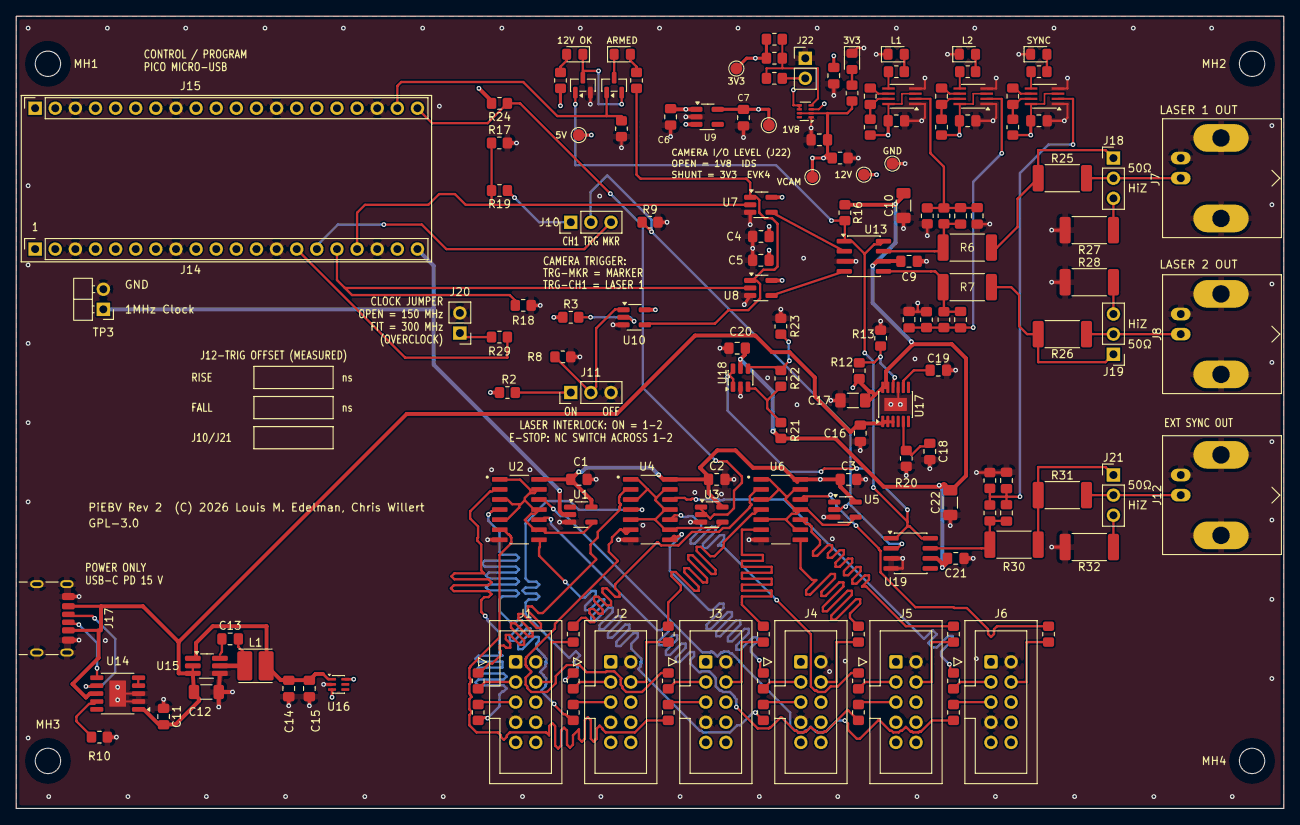
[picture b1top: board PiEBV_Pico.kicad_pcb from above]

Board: 4 copper layers, 160.0 x 100.0 mm, 159 parts (0 on the bottom side), 109 nets.

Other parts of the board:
MH1, MH2, MH3, MH4: MountingHole_3.2mm_M3

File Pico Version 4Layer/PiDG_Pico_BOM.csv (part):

"Reference","Value","Footprint","Qty","DNP","LCSC"
"C1-C5,C8,C9,C13,C20","0.1uF 50V X7R","Capacitor_SMD:C_0805_2012Metric_Pad1.18x1.45mm_HandSolder","9","","C49678"
"C6,C11,C16","1uF 50V X7R","Capacitor_SMD:C_0805_2012Metric_Pad1.18x1.45mm_HandSolder","3","","C28323"
"C7","2.2uF 16V X7R","Capacitor_SMD:C_0805_2012Metric_Pad1.18x1.45mm_HandSolder","1","","C28234"
"C10,C12,C17","10uF 50V X7R","Capacitor_SMD:C_1206_3216Metric_Pad1.33x1.80mm_HandSolder","3","","C89632"
"C14,C15","22uF 25V X5R","Capacitor_SMD:C_0805_2012Metric_Pad1.18x1.45mm_HandSolder","2","","C45783"
"C18","22nF 50V X7R","Capacitor_SMD:C_0805_2012Metric_Pad1.18x1.45mm_HandSolder","1","","C1729"
"C19","10nF 50V X7R","Capacitor_SMD:C_0805_2012Metric_Pad1.18x1.45mm_HandSolder","1","","C1710"
"L1","4.7uH, Isat >= 1.5 A","Inductor_SMD:L_Cenker_CKCS4030","1","","C354587"
"R2,R3,R5","3k3","Resistor_SMD:R_0805_2012Metric_Pad1.20x1.40mm_HandSolder","3","","C26010"
"R6,R7","68 1% 2W","Resistor_SMD:R_2512_6332Metric_Pad1.40x3.35mm_HandSolder","2","","C2793964"
"R25,R26","47 1% 2W (laser Hi-Z mode series)","Resistor_SMD:R_2512_6332Metric_Pad1.40x3.35mm_HandSolder","2","","C7209419"
"R27,R28","82 1% 2W (laser Hi-Z mode shunt)","Resistor_SMD:R_2512_6332Metric_Pad1.40x3.35mm_HandSolder","2","","C7468298"
"R8,R9,R17,R18,R24","10k","Resistor_SMD:R_0805_2012Metric_Pad1.20x1.40mm_HandSolder","5","","C17414"
"R10","56k","Resistor_SMD:R_0805_2012Metric_Pad1.20x1.40mm_HandSolder","1","","C17756"
"R12","100k 0.1%","Resistor_SMD:R_0805_2012Metric_Pad1.20x1.40mm_HandSolder","1","","C122537"
"R13","5.36k 0.1%","Resistor_SMD:R_0805_2012Metric_Pad1.20x1.40mm_HandSolder","1","","C706247"
"R16","100k","Resistor_SMD:R_0805_2012Metric_Pad1.20x1.40mm_HandSolder","1","","C149504"
"R19","100","Resistor_SMD:R_0805_2012Metric_Pad1.20x1.40mm_HandSolder","1","","C17408"
"R20","750 1%","Resistor_SMD:R_0805_2012Metric_Pad1.20x1.40mm_HandSolder","1","","C17818"
"R21","150k 1%","Resistor_SMD:R_0805_2012Metric_Pad1.20x1.40mm_HandSolder","1","","C17470"
"R22","1.2k 1%","Resistor_SMD:R_0805_2012Metric_Pad1.20x1.40mm_HandSolder","1","","C17379"
"R23","4.7k 1%","Resistor_SMD:R_0805_2012Metric_Pad1.20x1.40mm_HandSolder","1","","C17673"
"U1,U5","74LVC1G04","Package_TO_SOT_SMD:SOT-23-5_HandSoldering","2","","C7827"
"U3","74LVC1G00 (SN74LVC1G00DBVR, pixel-reset NAND)","Package_TO_SOT_SMD:SOT-23-5_HandSoldering","1","","C7826"
"U2,U4,U6","SN74LVC04AD","SN74LVC04AD:SOIC127P600X175-14N","3","","C485074"
"U7,U8,U10","74AHCT1G08","Package_TO_SOT_SMD:SOT-23-5_HandSoldering","3","","C113521"
"U9","NCP718xSN180","Package_TO_SOT_SMD:SOT-23-5_HandSoldering","1","","C892792"
"U12","74LVC1G17","Package_TO_SOT_SMD:SOT-23-5_HandSoldering","1","","C7836"
"U13","UCC27524","Package_SO:SOIC-8_3.9x4.9mm_P1.27mm","1","","C465729"
"U14","CH224A","Package_SO:SSOP-10-1EP_3.9x4.9mm_P1mm_EP2.1x3.3mm","1","","C42459160"
"U15","AP63205WU","Package_TO_SOT_SMD:TSOT-23-6_HandSoldering","1","","C2071056"
"U16","LM66100DCK","Package_TO_SOT_SMD:SOT-363_SC-70-6","1","","C2869734"
"U17","LT3065EDD#TRPBF (Analog Devices, adjustable)","Package_DFN_QFN:DFN-10-1EP_3x3mm_P0.5mm_EP1.65x2.38mm","1","","C670143"
"U18","TPS3700DDCR","Package_TO_SOT_SMD:SOT-23-6","1","","C33002"
"J1-J6","Conn_02x05_Odd_Even","Connector_IDC:IDC-Header_2x05_P2.54mm_Vertical","6","","C5665"
"J7,J8,J12","BNC 50R Kinghelm KH-BNC50-3511 (Laser 1 / Laser 2 / Pixel Reset)","PiDG_Local:BNC_Kinghelm_KH-BNC50-3511_Horizontal","3","","C2837587"
"J10,J11,J18,J19","Header 1x03 (J10 trigger select / J11 laser enable / J18, J19 laser output mode)","Connector_PinHeader_2.54mm:PinHeader_1x03_P2.54mm_Vertical","4","","C49257"
"(loose)","Jumper shunt, 2.54 mm 2-pin","-","4","Not placed on the board - fit J10 on 2-3, J11 on 1-2 (lasers enabled), J18 and J19 on 1-2 (50 ohm outputs) by hand","C100114"
"J16","Header 1x03 right-angle (EN/TRIG/GND)","PiDG_Local:PinHeader_1x03_P2.54mm_Horizontal_EdgeTrim","1","","C32713262"
"J17","USB-C receptacle 16P (HRO TYPE-C-31-M-12)","PiDG_Local:USB_C_Receptacle_HRO_TYPE-C-31-M-12_EdgeTrim","1","","C165948"
"TP3","Header 1x02 right-angle (1MHz sync + GND)","PiDG_Local:PinHeader_1x02_P2.54mm_Horizontal_EdgeTrim","1","","C32713261"
"TP4","Header 1x02 (CH2 monitor + GND)","Connector_PinHeader_2.54mm:PinHeader_1x02_P2.54mm_Vertical","1","","C32713268"
"J14,J15","Pico Socket A/B","Connector_PinSocket_2.54mm:PinSocket_1x20_P2.54mm_Vertical","2","","C2905423"
"U11","Raspberry Pi Pico 2 W","(no PCB footprint - plugs into J14/J15)","1","DNP - socket-mounted, do not place; source module separately",""
"MH1-MH4","M3 mounting hole","MountingHole:MountingHole_3.2mm_M3","4","Mechanical only - NPTH, nothing to place",""
"","","","","",""
"NOTE","U9 must be the FIXED 1.8 V NCP718 (NCP718xSN180, e.g. NCP718BSN180T1G or NCP718ASN180T1G)","Sets the camera I/O level. The IDS UE-39B0XCP-E I/O pins are 1.8 V sensor-level; do not substitute a 1.65 V, 1.7 V or 3.3 V option.","","",""
"NOTE","C6 is on +5V, C7 on +1V8 - use X7R, C6 rated >= 10 V","NCP718 needs >= 1 uF ceramic on its output for stability; C7 = 2.2 uF gives margin after DC-bias derating.","","",""
"NOTE","U12 must be a Schmitt-trigger part (74LVC1G17)","Gives the Pixel Reset BNC TTL-compatible thresholds and 0.5-0.8 V of hysteresis at 3.3 V. A plain 74LVC1G08/1G34 is not a substitute.","","",""
"NOTE","J16/TP3/J17 use PiDG_Local *_EdgeTrim footprint variants","Identical part and pad geometry to the stock footprints; only the silkscreen is clipped where the connector reaches the board edge. Order the standard parts.","","",""
"NOTE","R8 is a fail-safe interlock pull-down","Holds U10 pin 1 low when no jumper is fitted on J11, so the lasers default to DISABLED. R2 (3k3) still wins when the J11 1-2 jumper is fitted.","","",""
"NOTE","R9 is the J10 trigger-select pull-down","Holds PWM_TRIG_TAP (U5 input) low when no shunt is fitted on J10, so all six camera trigger lines idle low instead of floating.","","",""
"NOTE","U7/U8/U10 must be AHCT (TTL-input) parts, not LVC","At VCC = 5 V an LVC input needs 0.7 x VCC = 3.5 V to read high; the Pico drives these from 3.3 V GPIOs. AHCT reads high above 2.0 V.","","",""
"NOTE","R10 = 56k sets the USB PD request to 15 V","CH224A CFG1 table (datasheet Table 5-1): 6k8 = 9 V, 24k = 12 V, 56k = 15 V, 120k = 20 V, 210k = 28 V. Do not leave R10 off - an open CFG1 is outside the table. The laser outputs need a charger that offers 15 V (any USB-PD charger rated over 27 W).","","",""
"NOTE","U14 must be the CH224A (not the CH224K)","CH224A pin 1 (VHV) and pin 8 (VBUS) connect directly to VBUS_PD by copper, as the WCH CH224K-to-CH224A guide (datasheet 7.2.1) requires; R11/R15 of the CH224K design were removed. Do not fit a CH224K: it is discontinued, and its pin 1 is a 3.6 V VDD pin that VBUS_PD would destroy.","","",""
"NOTE","R12/R13 must be 0.1 % parts; R6/R7 1 %","They set the 11.8 V laser-driver rail and hence the LDP-V trigger amplitude (4.54-5.14 V into 50 ohm with U13 ROH 0-8.5 ohm, window 4.5-5.2 V). With 1 % divider resistors the worst-case corners fall outside the window.","","",""
"NOTE","U17 must be the ADJUSTABLE LT3065 (LT3065EDD), not a fixed LT3065-x","R12/R13 (100k/5.36k) set 11.8 V from the 600 mV ADJ reference. R20 (750 ohm) sets a 400 mA current limit and C18 (22 nF) on IMAX is required by the datasheet. Solder the exposed pad (two GND vias under it).","","",""
"NOTE","C9, C10, C17 see 12 V; C11, C12, C16 see up to 20 V","Use >= 25 V parts for C9/C10/C17 and >= 50 V for C11/C12/C16 (X7R). C12 is the only large cap on VBUS_PD (C11 and C16 are 1 uF each): keep total VBUS capacitance near the USB-C 10 uF sink limit.","","",""
"NOTE","U16 CE is tied to its VOUT (+5V)","That is TI's always-on reverse-blocking connection. With CE grounded the LM66100 does NOT block reverse current.","","",""
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

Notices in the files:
README.md:
License:
GNU General Public License, version 3 (GPL-3.0). See [LICENSE](LICENSE).
PiEBV_Pico.kicad_pcb:
PiEBV Rev 2  (C) 2026 Louis M. Edelman, Chris Willert
GPL-3.0
